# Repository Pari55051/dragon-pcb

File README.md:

# Dragon PCB

A creative, dragon-shaped PCB that comes alive in the dark — featuring glowing eyes and a beating heart. This project combines aesthetics with simple analog electronics.

---

## Features

- Heartbeat LEDs: 4 red LEDs light up in the dark making up its heart.
- Eye LED: A single LED lights up when ambient light is low.
- Growl Effect: Press a button to trigger a small vibration motor for a "growl" effect.

---

## Project Images

### Schematic Diagram

### PCB Layout

### 3D Model

---

## 🛠️ Components Used

| Component            | Quantity | Notes                                  |
|---------------------|----------|----------------------------------------|
| 5mm LEDs            | 5        | 4 for heart, 1 for eye                 |
| Photoresistor (GL5528) | 1        | Detects ambient light                 |
| 2N3904 Transistor  | 1        | used in the ambience light detecting circuit   |
| 220Ω Resistors      | 3        | For LEDs current limiting              |
| 4.7kΩ Resistor      | 1        | Bias resistor for photoresistor       |
| Vibration Motor (Disc) | 1     | Activated by push button              |
| Push Button (6mm)   | 1        | Momentary switch for vibration        |
| CR2032 Battery Holder | 1      | Power source                          |

---

> Slack Username: unowen
> 
> Slack ID: U08TH3JV9V4

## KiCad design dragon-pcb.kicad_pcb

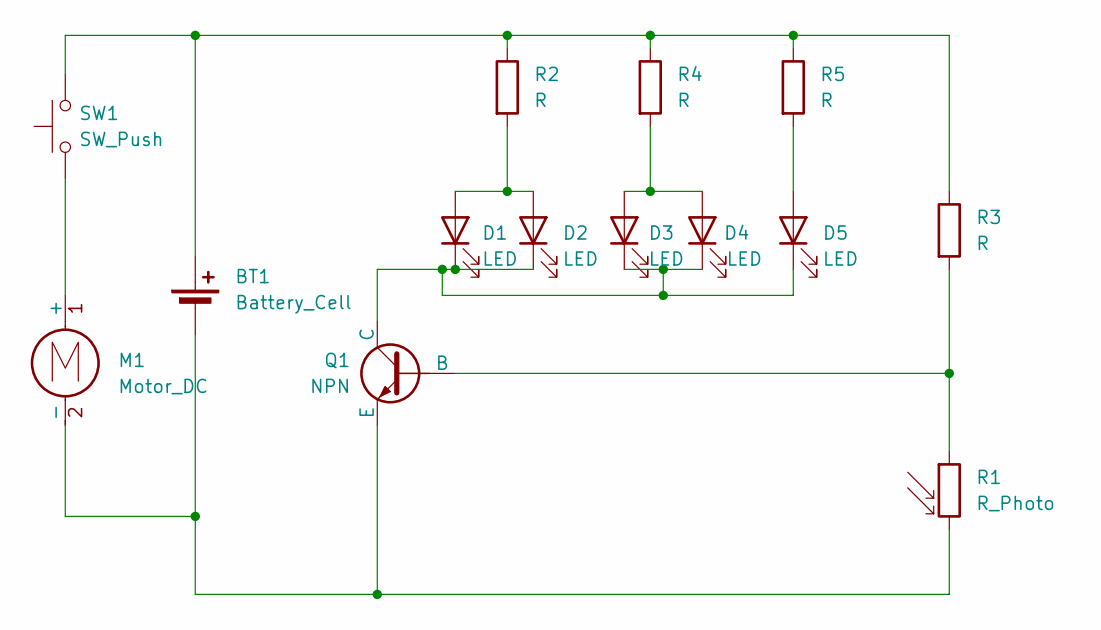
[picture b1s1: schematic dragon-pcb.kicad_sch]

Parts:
BT1: Battery_Cell; BatteryHolder_Keystone_3034_1x20mm
D1, D2, D3, D4, D5: LED; LED_D5.0mm
M1: Motor_DC; PinHeader_1x02_P2.54mm_Vertical
Q1: NPN; TO-92L_HandSolder
R1: R_Photo; R_LDR_5.1x4.3mm_P3.4mm_Vertical
R2, R3, R4, R5: R; R_Axial_DIN0207_L6.3mm_D2.5mm_P7.62mm_Horizontal
SW1: SW_Push; SW_PUSH_6mm

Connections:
unnamed: BT1.1 (+), R2.1, R3.1, R4.1, R5.1, SW1.2
unnamed: BT1.2 (-), M1.2 (-), Q1.3 (E), R1.2
unnamed: D1.2 (A), D2.2 (A), R2.2
unnamed: D1.1 (K), D2.1 (K), D3.1 (K), D4.1 (K), D5.1 (K), Q1.1 (C)
unnamed: D3.2 (A), D4.2 (A), R4.2
unnamed: D5.2 (A), R5.2
unnamed: M1.1 (+), SW1.1
unnamed: Q1.2 (B), R1.1, R3.2

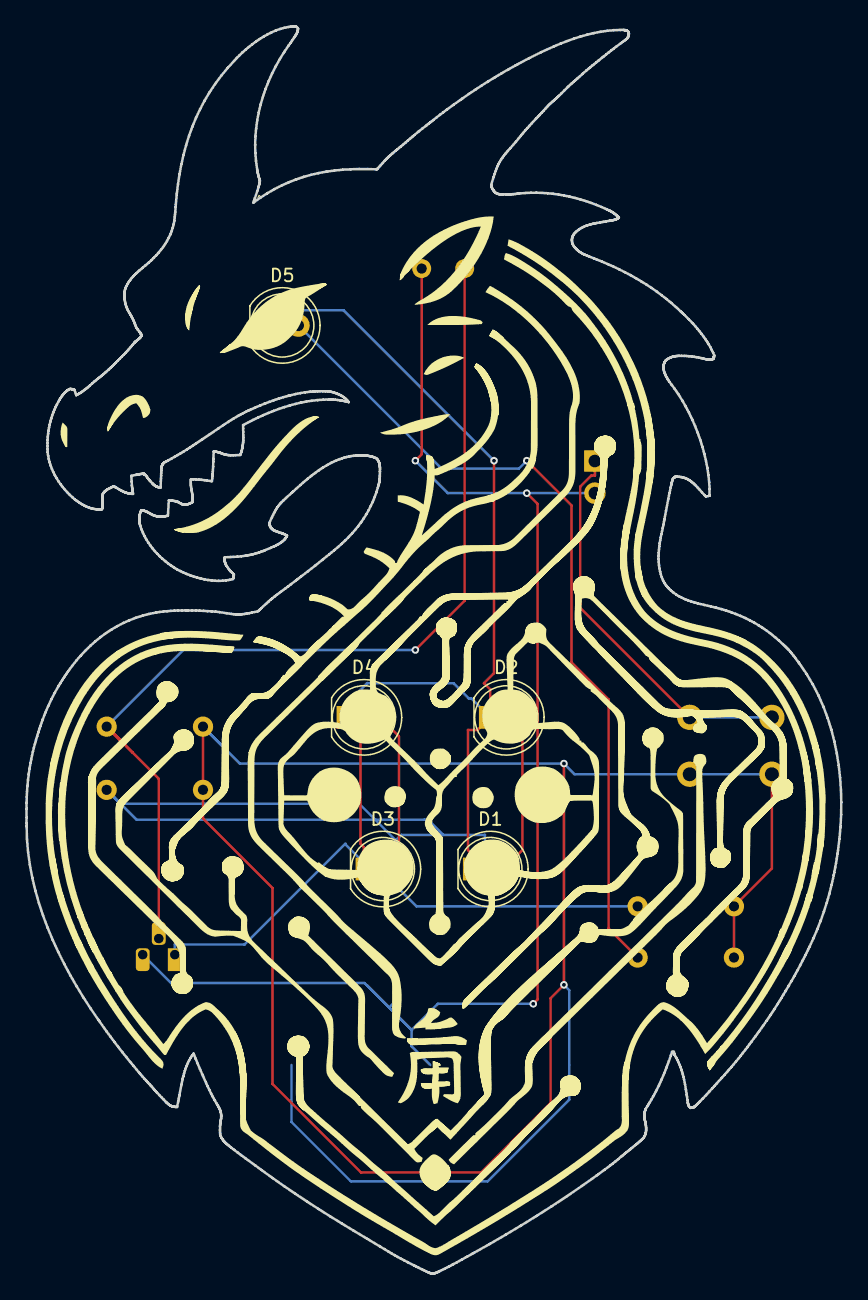
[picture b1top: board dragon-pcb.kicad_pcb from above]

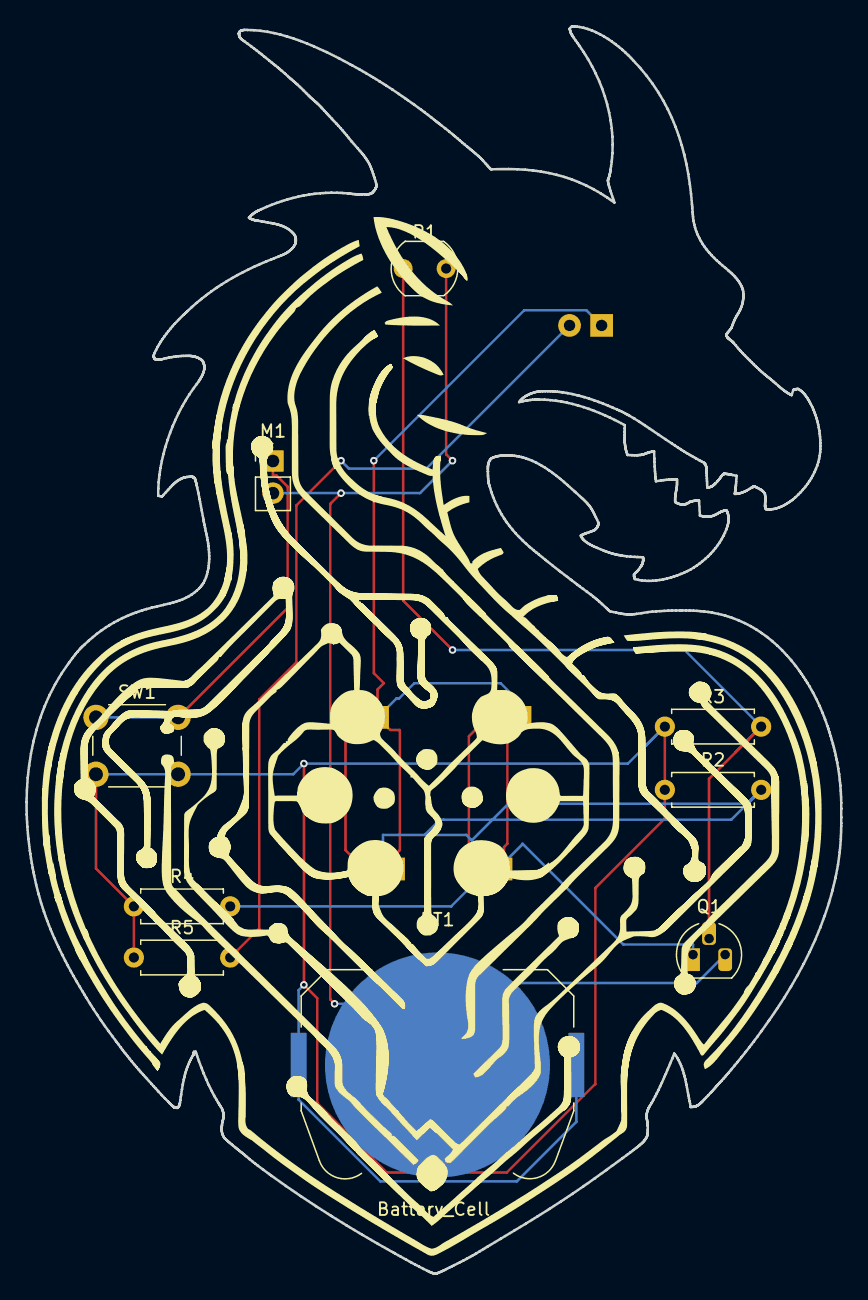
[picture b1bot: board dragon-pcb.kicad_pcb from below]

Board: 2 copper layers, 64.4 x 98.6 mm, 14 parts (9 on the bottom side), 8 nets.

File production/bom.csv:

Designator,Footprint,Quantity,Value,LCSC Part #
BT1,BatteryHolder_Keystone_3034_1x20mm,1,Battery_Cell,
"D1, D2, D3, D4, D5",LED_D5.0mm,5,LED,
M1,PinHeader_1x02_P2.54mm_Vertical,1,Motor_DC,
Q1,TO-92L_HandSolder,1,NPN,
R1,R_LDR_5.1x4.3mm_P3.4mm_Vertical,1,R_Photo,
"R2, R3, R4, R5",R_Axial_DIN0207_L6.3mm_D2.5mm_P7.62mm_Horizontal,4,R,
SW1,SW_PUSH_6mm,1,SW_Push,
